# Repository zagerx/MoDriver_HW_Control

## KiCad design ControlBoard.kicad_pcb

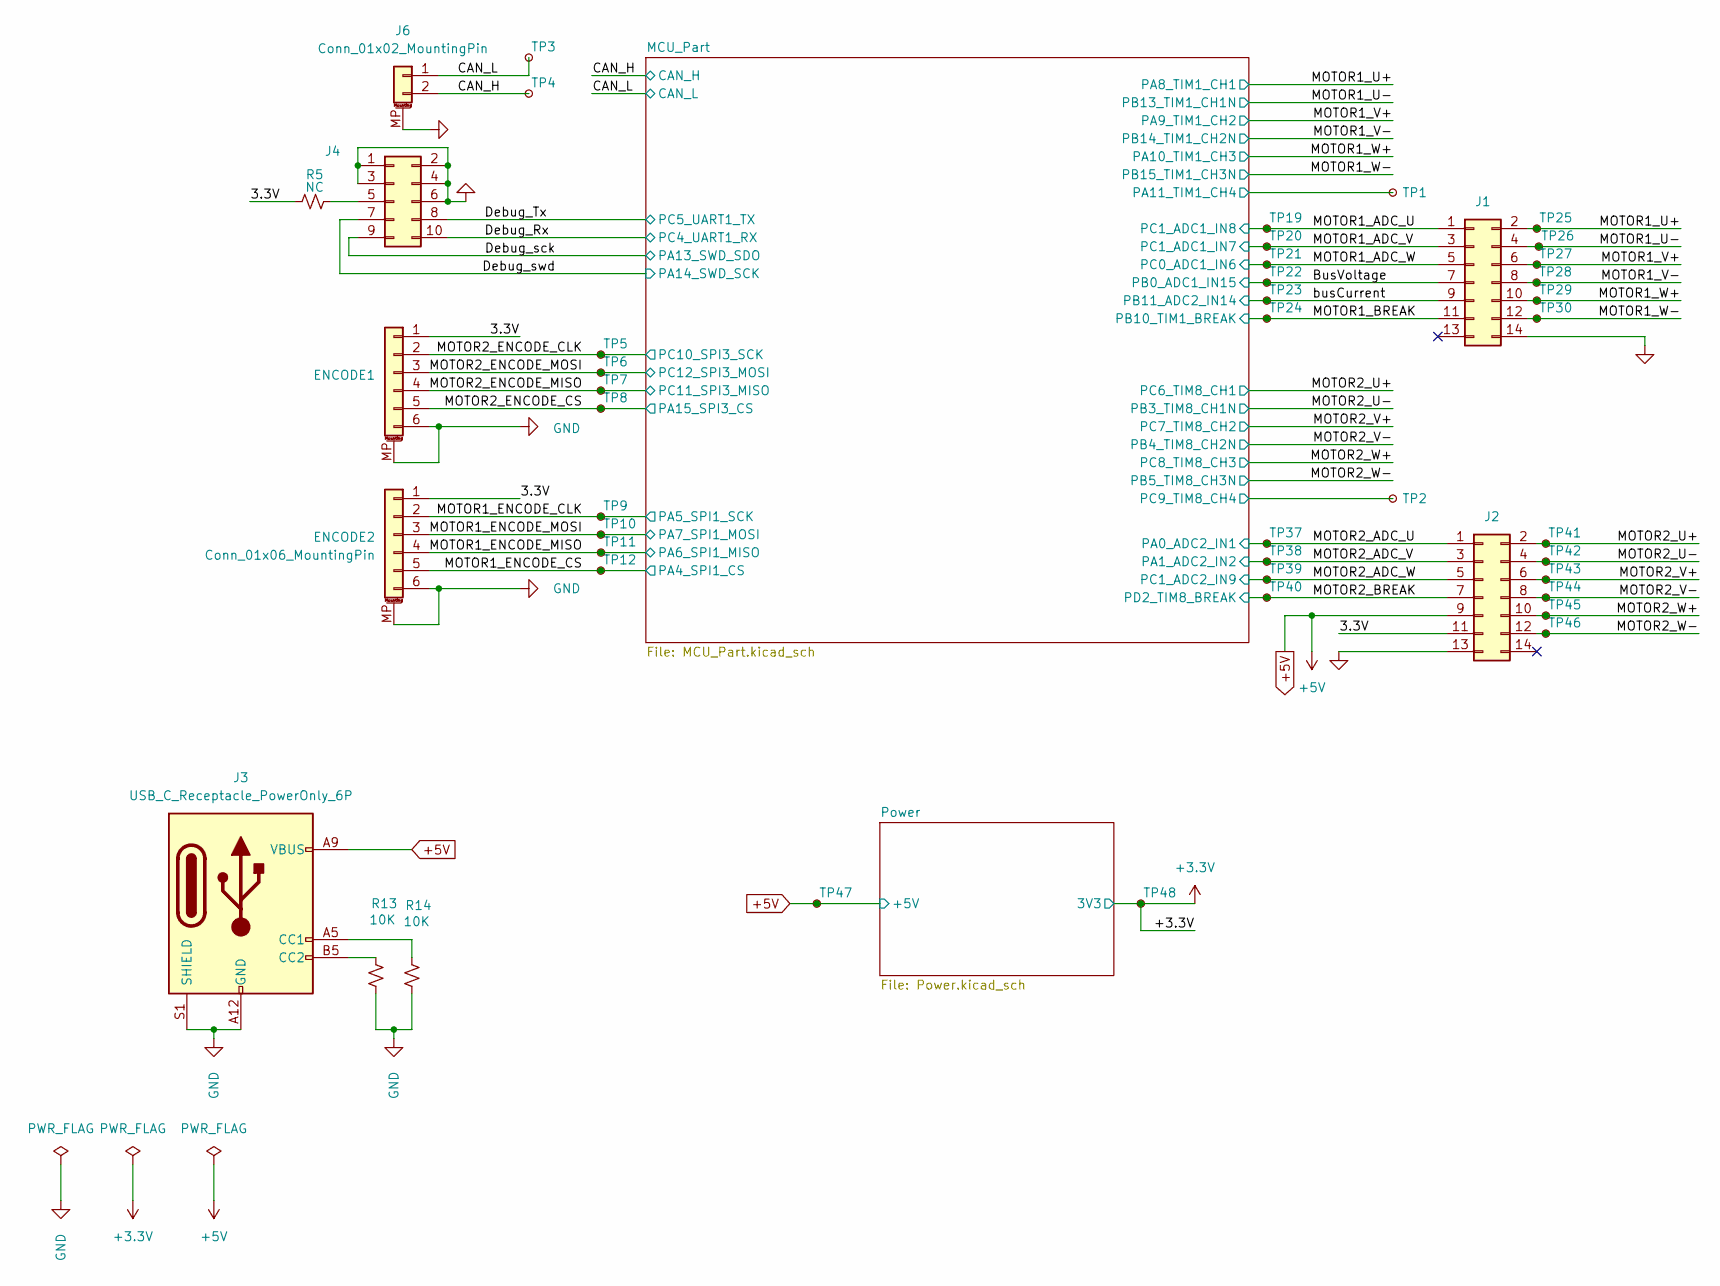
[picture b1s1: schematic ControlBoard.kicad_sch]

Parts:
ENCODE1: ENCODE1; JST_SH_BM06B-SRSS-TB_1x06-1MP_P1.00mm_Horizontal
ENCODE2: Conn_01x06_MountingPin; JST_SH_BM06B-SRSS-TB_1x06-1MP_P1.00mm_Horizontal
J1, J2: Conn_02x07_Odd_Even; PinSocket_2x07_P1.27mm_Vertical_SMD
J3: USB_C_Receptacle_PowerOnly_6P; USB_C_Receptacle_GCT_USB4125-xx-x-0190_6P_TopMnt_Horizontal
J4: Conn_02x05_Odd_Even; Box_Head_1.27mm_SMD_Vertical_02x05
J6: Conn_01x02_MountingPin; JST_SH_BM02B-SRSS-TB_1x02-1MP_P1.00mm_Horizontal
R5: NC; R_0603_1608Metric_Pad0.98x0.95mm_HandSolder
R13, R14: 10K; R_0603_1608Metric_Pad0.98x0.95mm_HandSolder
TP1, TP2, TP3, TP4, TP5, TP6, TP7, TP8, TP9, TP10, TP11, TP12, TP19, TP20, TP21, TP22, TP23, TP24, TP25, TP26, TP27, TP28, TP29, TP30, TP37, TP38, TP39, TP40, TP41, TP42, TP43, TP44, TP45, TP46, TP47, TP48: TestPoint_Small; TestPoint_Pad_D1.0mm

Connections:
+3.3V: TP48.1; also elsewhere on the board
+5V: J2.9, J3.A9 (VBUS), J3.B9 (VBUS), TP47.1; also elsewhere on the board
/3.3V: ENCODE1.1, ENCODE2.1, J2.11, R5.1
/BusVoltage: J1.7, TP22.1; also elsewhere on the board
/CAN_H: J6.2, TP4.1; also elsewhere on the board
/CAN_L: J6.1, TP3.1; also elsewhere on the board
/Debug_Rx: J4.10; also elsewhere on the board
/Debug_Tx: J4.8; also elsewhere on the board
/Debug_sck: J4.9; also elsewhere on the board
/Debug_swd: J4.7; also elsewhere on the board
/MCU_Part/PA11_TIM1_CH4: TP1.1; also elsewhere on the board
/MCU_Part/PC9_TIM8_CH4: TP2.1; also elsewhere on the board
/MOTOR1_ADC_U: J1.1, TP19.1; also elsewhere on the board
/MOTOR1_ADC_V: J1.3, TP20.1; also elsewhere on the board
/MOTOR1_ADC_W: J1.5, TP21.1; also elsewhere on the board
/MOTOR1_BREAK: J1.11, TP24.1; also elsewhere on the board
/MOTOR1_ENCODE_CLK: ENCODE2.2, TP9.1; also elsewhere on the board
/MOTOR1_ENCODE_CS: ENCODE2.5, TP12.1; also elsewhere on the board
/MOTOR1_ENCODE_MISO: ENCODE2.4, TP11.1; also elsewhere on the board
/MOTOR1_ENCODE_MOSI: ENCODE2.3, TP10.1; also elsewhere on the board
/MOTOR1_U+: J1.2, TP25.1; also elsewhere on the board
/MOTOR1_U-: J1.4, TP26.1; also elsewhere on the board
/MOTOR1_V+: J1.6, TP27.1; also elsewhere on the board
/MOTOR1_V-: J1.8, TP28.1; also elsewhere on the board
/MOTOR1_W+: J1.10, TP29.1; also elsewhere on the board
/MOTOR1_W-: J1.12, TP30.1; also elsewhere on the board
/MOTOR2_ADC_U: J2.1, TP37.1; also elsewhere on the board
/MOTOR2_ADC_V: J2.3, TP38.1; also elsewhere on the board
/MOTOR2_ADC_W: J2.5, TP39.1; also elsewhere on the board
/MOTOR2_BREAK: J2.7, TP40.1; also elsewhere on the board
/MOTOR2_ENCODE_CLK: ENCODE1.2, TP5.1; also elsewhere on the board
/MOTOR2_ENCODE_CS: ENCODE1.5, TP8.1; also elsewhere on the board
/MOTOR2_ENCODE_MISO: ENCODE1.4, TP7.1; also elsewhere on the board
/MOTOR2_ENCODE_MOSI: ENCODE1.3, TP6.1; also elsewhere on the board
/MOTOR2_U+: J2.2, TP41.1; also elsewhere on the board
/MOTOR2_U-: J2.4, TP42.1; also elsewhere on the board
/MOTOR2_V+: J2.6, TP43.1; also elsewhere on the board
/MOTOR2_V-: J2.8, TP44.1; also elsewhere on the board
/MOTOR2_W+: J2.10, TP45.1; also elsewhere on the board
/MOTOR2_W-: J2.12, TP46.1; also elsewhere on the board
/busCurrent: J1.9, TP23.1; also elsewhere on the board
GND: ENCODE1.6, ENCODE1.MP (MountPin), ENCODE2.6, ENCODE2.MP (MountPin), J1.14, J2.13, J3.A12 (GND), J3.B12 (GND), J3.S1 (SHIELD), J4.1, J4.2, J4.3, J4.4, J4.6, J6.MP (MountPin), R13.2, R14.2; also elsewhere on the board
unnamed: J3.A5 (CC1), R14.1
unnamed: J3.B5 (CC2), R13.1
unnamed: J4.5, R5.2

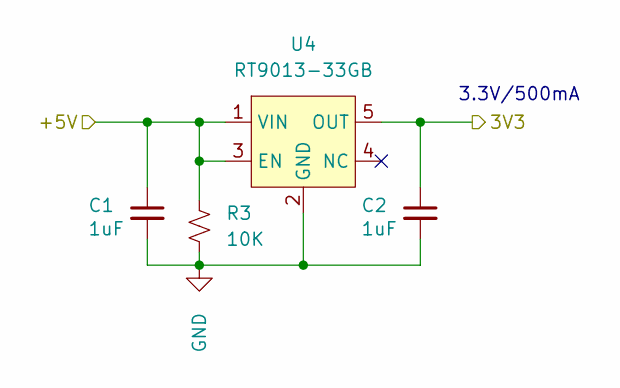
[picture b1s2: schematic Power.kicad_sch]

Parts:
C1, C2: 1uF; C_0603_1608Metric_Pad1.08x0.95mm_HandSolder
R3: 10K; R_0603_1608Metric_Pad0.98x0.95mm_HandSolder
U4: RT9013-33GB; SOT-23-5

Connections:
+3.3V: C2.1, U4.5 (OUT); also elsewhere on the board
+5V: C1.1, R3.1, U4.1 (VIN), U4.3 (EN); also elsewhere on the board
GND: C1.2, C2.2, R3.2, U4.2 (GND); also elsewhere on the board

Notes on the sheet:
3.3V/500mA

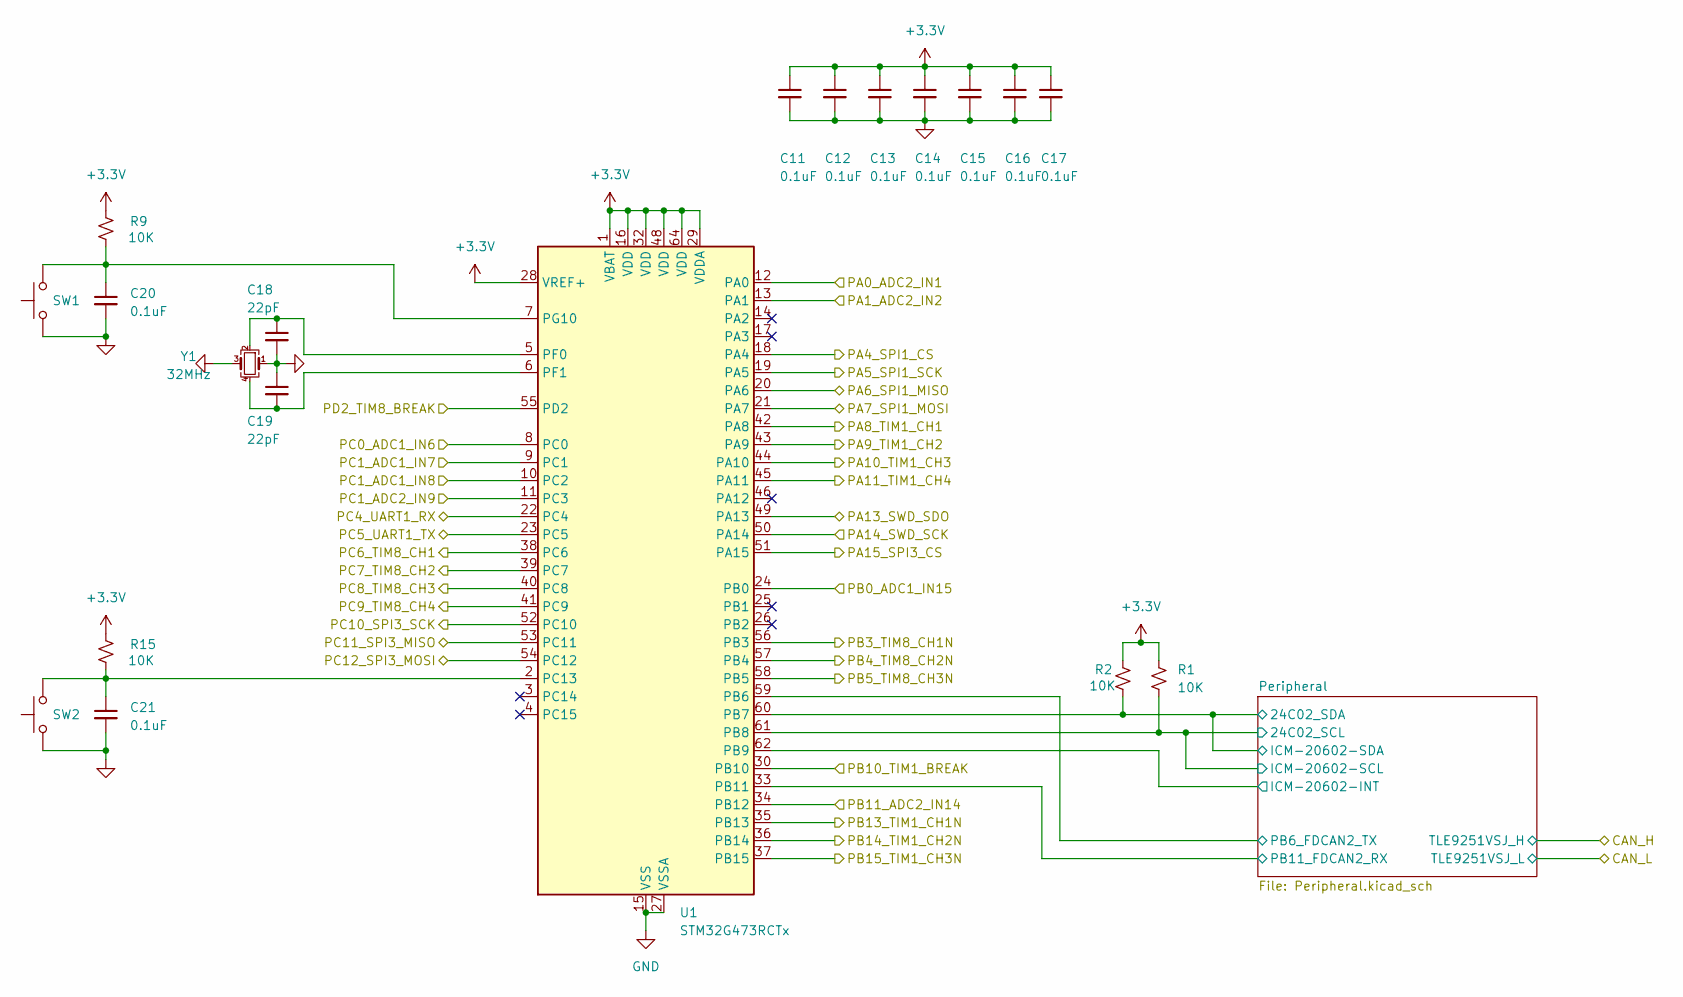
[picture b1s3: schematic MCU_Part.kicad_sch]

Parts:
C11, C12, C13, C14, C15, C16, C17, C20, C21: 0.1uF; C_0603_1608Metric_Pad1.08x0.95mm_HandSolder
C18, C19: 22pF; C_0603_1608Metric_Pad1.08x0.95mm_HandSolder
R1, R2, R9, R15: 10K; R_0603_1608Metric_Pad0.98x0.95mm_HandSolder
SW1, SW2: SW_Push; SW_SPST_CK_RS282G05A3
U1: STM32G473RCTx; LQFP-64_10x10mm_P0.5mm
Y1: 32MHz; Crystal_SMD_3225-4Pin_3.2x2.5mm

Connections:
+3.3V: C11.1, C12.1, C13.1, C14.1, C15.1, C16.1, C17.1, R1.1, R2.1, R9.1, R15.1, U1.1 (VBAT), U1.16 (VDD), U1.28 (VREF+), U1.29 (VDDA), U1.32 (VDD), U1.48 (VDD), U1.64 (VDD); also elsewhere on the board
/BusVoltage: U1.24 (PB0); also elsewhere on the board
/Debug_Rx: U1.22 (PC4); also elsewhere on the board
/Debug_Tx: U1.23 (PC5); also elsewhere on the board
/Debug_sck: U1.49 (PA13); also elsewhere on the board
/Debug_swd: U1.50 (PA14); also elsewhere on the board
/MCU_Part/PA11_TIM1_CH4: U1.45 (PA11); also elsewhere on the board
/MCU_Part/PC9_TIM8_CH4: U1.41 (PC9); also elsewhere on the board
/MCU_Part/Peripheral/24C02_SCL: R1.2, U1.61 (PB8); also elsewhere on the board
/MCU_Part/Peripheral/24C02_SDA: R2.2, U1.60 (PB7); also elsewhere on the board
/MCU_Part/Peripheral/ICM-20602-INT: U1.62 (PB9); also elsewhere on the board
/MCU_Part/Peripheral/PB6_FDCAN2_TX: U1.59 (PB6); also elsewhere on the board
/MCU_Part/Peripheral/PB11_FDCAN2_RX: U1.33 (PB11); also elsewhere on the board
/MOTOR1_ADC_U: U1.10 (PC2); also elsewhere on the board
/MOTOR1_ADC_V: U1.9 (PC1); also elsewhere on the board
/MOTOR1_ADC_W: U1.8 (PC0); also elsewhere on the board
/MOTOR1_BREAK: U1.30 (PB10); also elsewhere on the board
/MOTOR1_ENCODE_CLK: U1.19 (PA5); also elsewhere on the board
/MOTOR1_ENCODE_CS: U1.18 (PA4); also elsewhere on the board
/MOTOR1_ENCODE_MISO: U1.20 (PA6); also elsewhere on the board
/MOTOR1_ENCODE_MOSI: U1.21 (PA7); also elsewhere on the board
/MOTOR1_U+: U1.42 (PA8); also elsewhere on the board
/MOTOR1_U-: U1.35 (PB13); also elsewhere on the board
/MOTOR1_V+: U1.43 (PA9); also elsewhere on the board
/MOTOR1_V-: U1.36 (PB14); also elsewhere on the board
/MOTOR1_W+: U1.44 (PA10); also elsewhere on the board
/MOTOR1_W-: U1.37 (PB15); also elsewhere on the board
/MOTOR2_ADC_U: U1.12 (PA0); also elsewhere on the board
/MOTOR2_ADC_V: U1.13 (PA1); also elsewhere on the board
/MOTOR2_ADC_W: U1.11 (PC3); also elsewhere on the board
/MOTOR2_BREAK: U1.55 (PD2); also elsewhere on the board
/MOTOR2_ENCODE_CLK: U1.52 (PC10); also elsewhere on the board
/MOTOR2_ENCODE_CS: U1.51 (PA15); also elsewhere on the board
/MOTOR2_ENCODE_MISO: U1.53 (PC11); also elsewhere on the board
/MOTOR2_ENCODE_MOSI: U1.54 (PC12); also elsewhere on the board
/MOTOR2_U+: U1.38 (PC6); also elsewhere on the board
/MOTOR2_U-: U1.56 (PB3); also elsewhere on the board
/MOTOR2_V+: U1.39 (PC7); also elsewhere on the board
/MOTOR2_V-: U1.57 (PB4); also elsewhere on the board
/MOTOR2_W+: U1.40 (PC8); also elsewhere on the board
/MOTOR2_W-: U1.58 (PB5); also elsewhere on the board
/busCurrent: U1.34 (PB12); also elsewhere on the board
GND: C11.2, C12.2, C13.2, C14.2, C15.2, C16.2, C17.2, C18.2, C19.1, C20.2, C21.2, SW1.1, SW2.1, U1.15 (VSS), U1.27 (VSSA), U1.31 (VSS), U1.47 (VSS), U1.63 (VSS), Y1.1, Y1.3; also elsewhere on the board
unnamed: C21.1, R15.2, SW2.2, U1.2 (PC13)
unnamed: C18.1, U1.5 (PF0), Y1.2
unnamed: C19.2, U1.6 (PF1), Y1.4
unnamed: C20.1, R9.2, SW1.2, U1.7 (PG10)

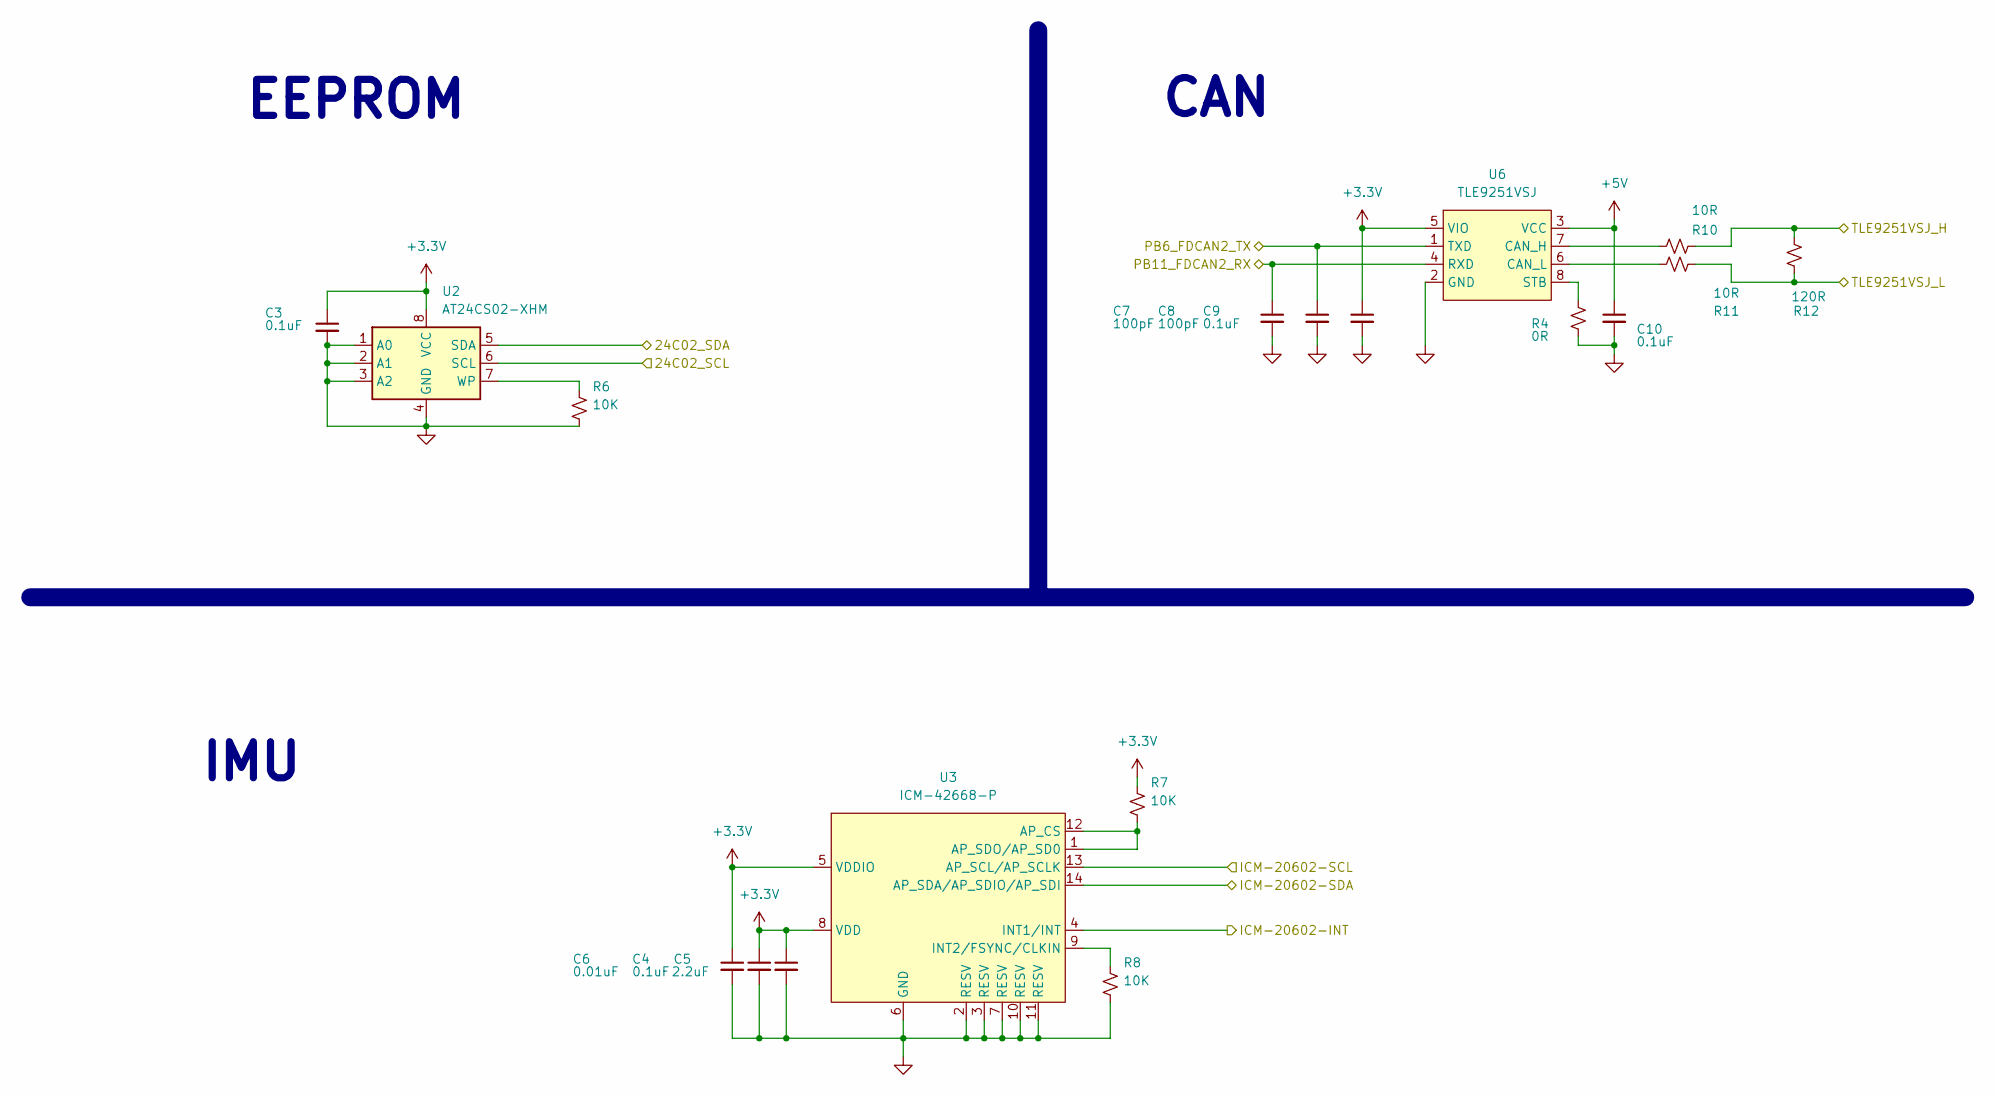
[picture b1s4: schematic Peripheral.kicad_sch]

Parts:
C3, C4, C9, C10: 0.1uF; C_0603_1608Metric_Pad1.08x0.95mm_HandSolder
C5: 2.2uF; C_0603_1608Metric_Pad1.08x0.95mm_HandSolder
C6: 0.01uF; C_0603_1608Metric_Pad1.08x0.95mm_HandSolder
C7, C8: 100pF; C_0603_1608Metric_Pad1.08x0.95mm_HandSolder
R4: 0R; R_0603_1608Metric_Pad0.98x0.95mm_HandSolder
R6, R7, R8: 10K; R_0603_1608Metric_Pad0.98x0.95mm_HandSolder
R10, R11: 10R; R_0603_1608Metric_Pad0.98x0.95mm_HandSolder
R12: 120R; R_0603_1608Metric_Pad0.98x0.95mm_HandSolder
U2: AT24CS02-XHM; TSSOP-8_4.4x3mm_P0.65mm
U3: ICM-42668-P; Bosch_LGA-14_3x2.5mm_P0.5mm
U6: TLE9251VSJ; Infineon_PG-DSO-8-24_4x5mm

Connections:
+3.3V: C3.1, C4.1, C5.1, C6.1, C9.1, R7.1, U2.8 (VCC), U3.5 (VDDIO), U3.8 (VDD), U6.5 (VIO); also elsewhere on the board
+5V: C10.1, U6.3 (VCC); also elsewhere on the board
/CAN_H: R10.2, R12.1; also elsewhere on the board
/CAN_L: R11.2, R12.2; also elsewhere on the board
/MCU_Part/Peripheral/24C02_SCL: U2.6 (SCL), U3.13 (AP_SCL/AP_SCLK); also elsewhere on the board
/MCU_Part/Peripheral/24C02_SDA: U2.5 (SDA), U3.14 (AP_SDA/AP_SDIO/AP_SDI); also elsewhere on the board
/MCU_Part/Peripheral/ICM-20602-INT: U3.4 (INT1/INT); also elsewhere on the board
/MCU_Part/Peripheral/PB6_FDCAN2_TX: C8.1, U6.1 (TXD); also elsewhere on the board
/MCU_Part/Peripheral/PB11_FDCAN2_RX: C7.1, U6.4 (RXD); also elsewhere on the board
GND: C3.2, C4.2, C5.2, C6.2, C7.2, C8.2, C9.2, C10.2, R4.1, R6.2, R8.2, U2.1 (A0), U2.2 (A1), U2.3 (A2), U2.4 (GND), U3.2 (RESV), U3.3 (RESV), U3.6 (GND), U3.7 (RESV), U3.10 (RESV), U3.11 (RESV), U6.2 (GND); also elsewhere on the board
unnamed: R6.1, U2.7 (WP)
unnamed: R7.2, U3.1 (AP_SDO/AP_SD0), U3.12 (AP_CS)
unnamed: R8.1, U3.9 (INT2/FSYNC/CLKIN)
unnamed: R10.1, U6.7 (CAN_H)
unnamed: R11.1, U6.6 (CAN_L)
unnamed: R4.2, U6.8 (STB)

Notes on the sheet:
CAN
IMU
EEPROM

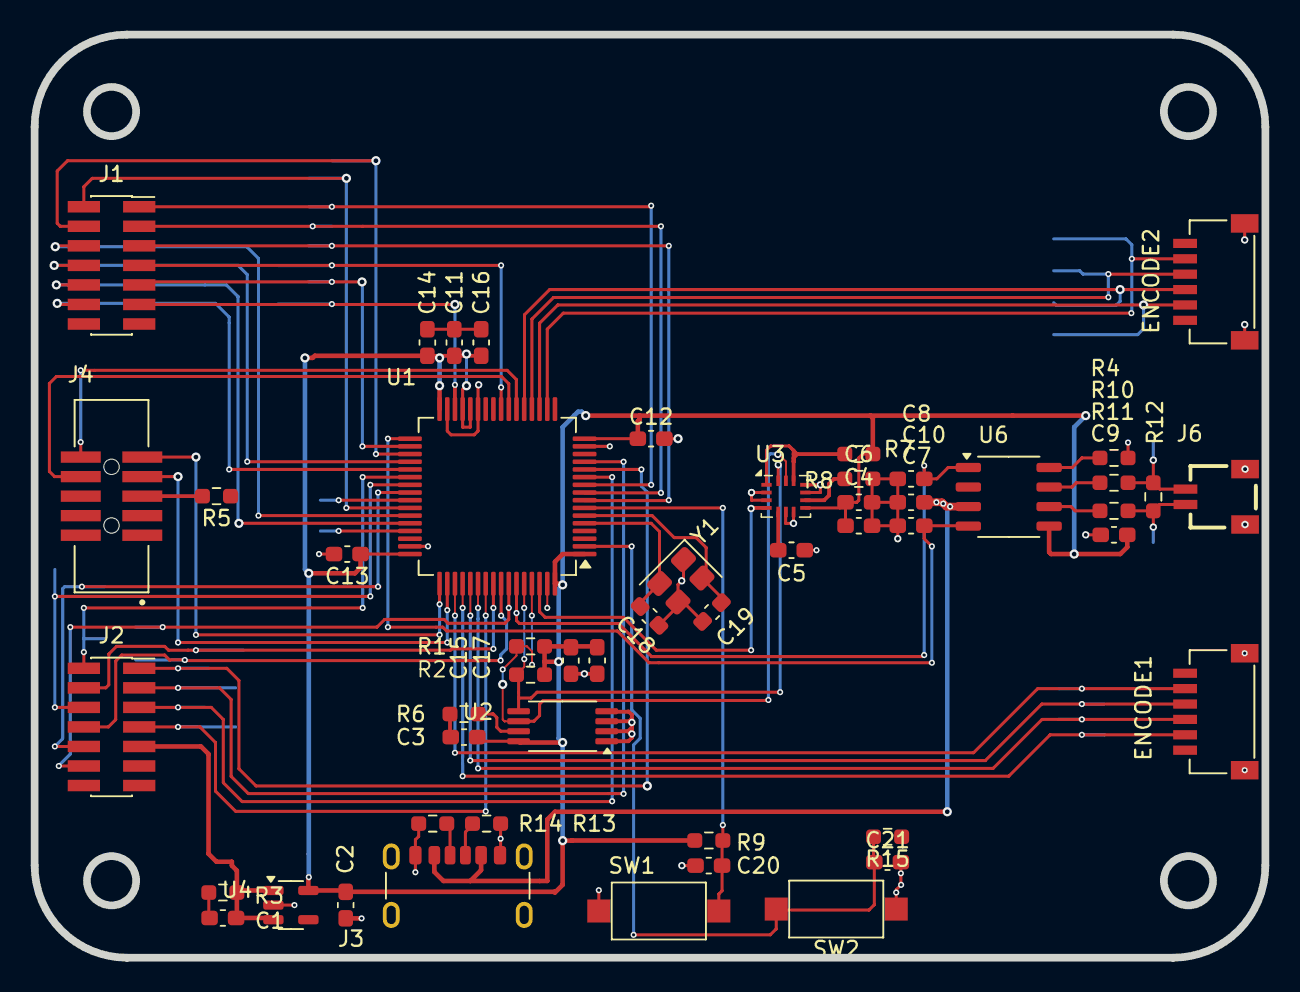
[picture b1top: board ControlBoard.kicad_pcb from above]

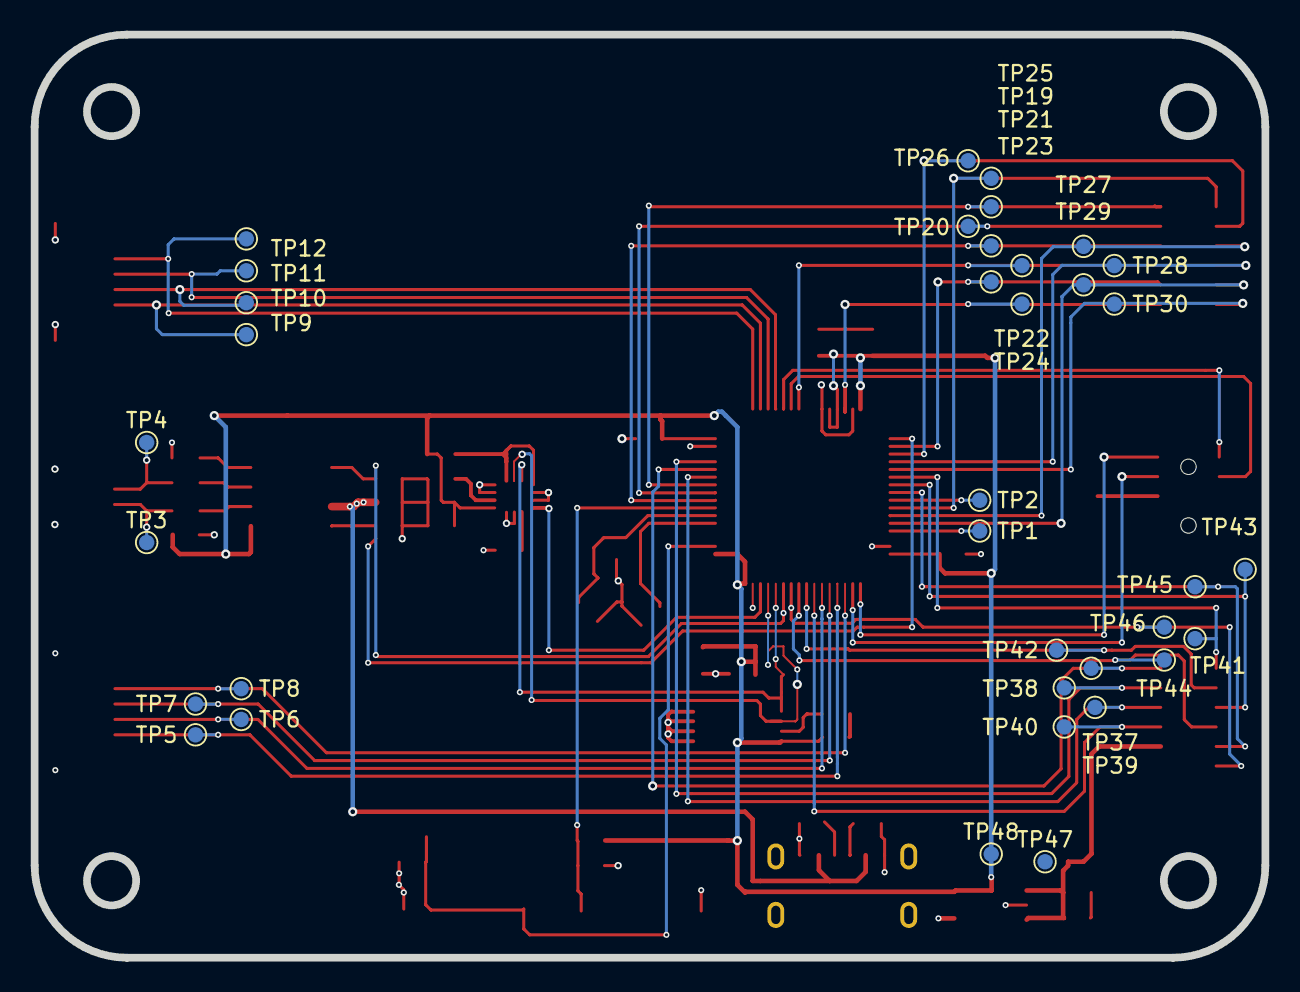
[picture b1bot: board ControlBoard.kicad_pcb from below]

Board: 2 copper layers, 80.0 x 60.0 mm, 87 parts (36 on the bottom side), 60 nets.

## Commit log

2025-07-28 init commit
2025-07-31 增加kicad工程
2025-07-31 增加忽略文件
2025-08-01 增加部分接口
2025-08-04 增加PWM/SPI部分接口
2025-08-04 增加ADC采样，优化PWM
2025-08-04 完成部分I2C/FDCAN引脚分配
2025-08-05 增加3.3V电路
2025-08-05 优化EEPROM电路
2025-08-05 优化IMU电路
2025-08-06 优化接口
2025-08-06 增加网表及PCB文件
2025-08-08 重新分配端子封装
2025-08-17 修改板框
2025-08-29 增加晶振电路
2025-09-03 PCB初布局
2025-09-15 增加测试点
2025-09-15 增加typeC接口
2025-09-16 优化Type-C电路
2025-09-18 优化布局20250919
2025-09-19 优化PCB布线20250919
2025-09-19 信号线布线完成
